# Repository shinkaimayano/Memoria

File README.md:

# Memoria

A hotswap drop-in PCB for the [V4N4G0N](https://trashman.wiki/keyboards/v4n4g0n) family of keyboards.

## Features
  
- RP2040 MCU with 16MBs (128Mbs) of flash storage.  
- Has integrated aRGB LED indicators (SK6812MINI-E), replacing the soldered single-color THT LEDs of the original.  
  - These pins are broken out if you want to add underglow as well.
- Overcurrent and ESD protection.
- Curved traces, teardrops, and a hatched copper fill for a prettier look.  

The firmware, found [here](https://github.com/shinkaimayano/Firmwares/tree/main/memoria/rev2.0), can be flashed by dragging and dropping the .uf2 file into the Mass Storage Device (MSD) that shows up on the first plug-in of the PCB. Afterwards, it is recommended to use Bootmagic (by holding down the top left key on plug-in) to put it into bootloader. You can short the two pads underneath while plugging it in as a last resort.

## Layout and Renders

This PCB supports the [Jetvan](https://trashman.wiki/pcbs/jetvan) (6.25u) and [Minisub](https://trashman.wiki/en/community/pcbs/minisub) (2.75u-2.25u-1.25u) bottom rows. The KLE can be found [here](http://www.keyboard-layout-editor.com/#/gists/7a51d1ecabd92635db48dc4a6c9a3fa1).

## Ordering

Current Status: **Working** (***Order at your own risk!***)

The following guide is for ordering these PCBs from [JLCPCB](https://jlcpcb.com/).

1. Click the "Order now" text and upload the zipped gerbers via draging-and-dropping or locating the file via your file explorer.
2. After it finishes uploading, it may or may not display a preview of what it should it look like. If it doesn't, it won't autofill in the dimensions of the PCB. Input these numbers (242.8875mm x 96.7850mm) into the dimensions box if so.
3. You can now pick out your preferred PCB color, finish, and decide if you want to remove the order number silkscreen on the PCB for a bit extra along with some other extra options you can choose.
4. Check the option for "PCB Assembly" and change the assembly side to the bottom. After that, you can select if you want to have five PCBs assembled or two of them.
   - Having five PCBs assembled compared to two is a minor price increase with the benefit of:
      - Having an easy replacement if something goes wrong.
      - Wanting to use a different case without disassembling another build.
      - Being able to give/sell to others that might want it.
5. Upload the BOM & CPL in each box respectively and select "Office Appliance and Accessories &rarr; Keyboard HS Code 847330" for the description.
6. On the next page, you can see the output of the BOM file and check if the parts are correct or if they're out of stock or not. If the hotswap sockets are out of stock, you have three options. You can either:
   - Preorder part number "C5156480" into your parts library and order the PCBs when they arrive.
   - Wait for them to restock.
   - Order without the sockets pre-assembled and solder them on yourself.
7. On the final page, you can now see a preview of where the components are going to be placed and their respective rotations based on the CPL file. Review the positions and rotations and fix them if you need to.
8. At this point, you should be now able to place your order unless you want to order other PCBs with it! Make sure to respond to any e-mails that they send.
   - I would make sure to double check the parts placement after they do their DFM analysis as they changed the rotations of the horizontal diodes even though they were correct in the order preview. (I didn't notice this beforehand and had to fix the PCBs when they arrived. This could have been remedied by selecting "Confirm Parts Placement" after checking the option for "PCB Assembly" in step 4.)

Plate files are available from [Kiser Design's](https://kiserdesigns.bigcartel.com) [Monorail](https://trashman.wiki/en/community/pcbs/monorail) repository ([here](https://github.com/KiserDesigns/monorail)). The plate layout should be either be "Jet" or "Combined" and whether to choose the compression-style plate (V4N R1/2) or the bottom/top mount plate (V3N a.k.a. Hullagon) depends on what case you are using.

- I highly recommend getting your plates cut from [P3D  Store](https://p3dstore.com/products/switch-plates) as they have several materials that are loved by the community. They currently only offer plastic plates though so:
  - If you want a metal plate, you can have them cut from either [SendCutSend](https://sendcutsend.com/) (USA) or [LaserBoost](https://www.laserboost.com/) (EU) by directly uploading the .dxf file to their website.
  - If you want a FR4 plate, you'll need to do a bit of extra work. You can watch [this tutorial](https://www.youtube.com/watch?v=VofKu8A7l3c) if don't know how to convert a .dxf file into usable gerber files. You can order these alongside the PCBs as well.
    - If you have JLCPCB fabricate them, you will most likely get slapped with a fine for needing an excess amount of time to mill out the switch cutouts, wearing out their bits in the process.

## Notes

- Debug pins (SWDIO & SWCLK) are not broken out.
  - As the bootloader is stored in the RP2040's ROM, it would be pratically impossible to brick it.
- Slightly updated the edge cuts to make it a one-to-one match to the original R3 plate file.
  - Fillets were too big and edges were off by a smidge.
- Two switches were flipped on R3 instead of putting the MCU on the bottom row for sanity reasons.
  - This shouldn't effect anything excepting needing a little more attention when installing switches.
- Changed matrix connections of two switches to prevent any chance of them shorting each other compared to previous revisions.
- Plating was added to the bottom stabilizer holes so GND can't be accidentally shorted when using screw-in stabilizers.
- The flower silkscreen was removed in favor for a user-friendly key sizing guide.
- The aRGB on the PCB are slightly off in the vertical direction compared to the plate for cleaner routing.
- The libraries used for this project are my own and [marbastlib](https://github.com/ebastler/marbastlib).
- You need at least KiCad 6 Nightly (2022-10-28 and beyond) to open the source files.

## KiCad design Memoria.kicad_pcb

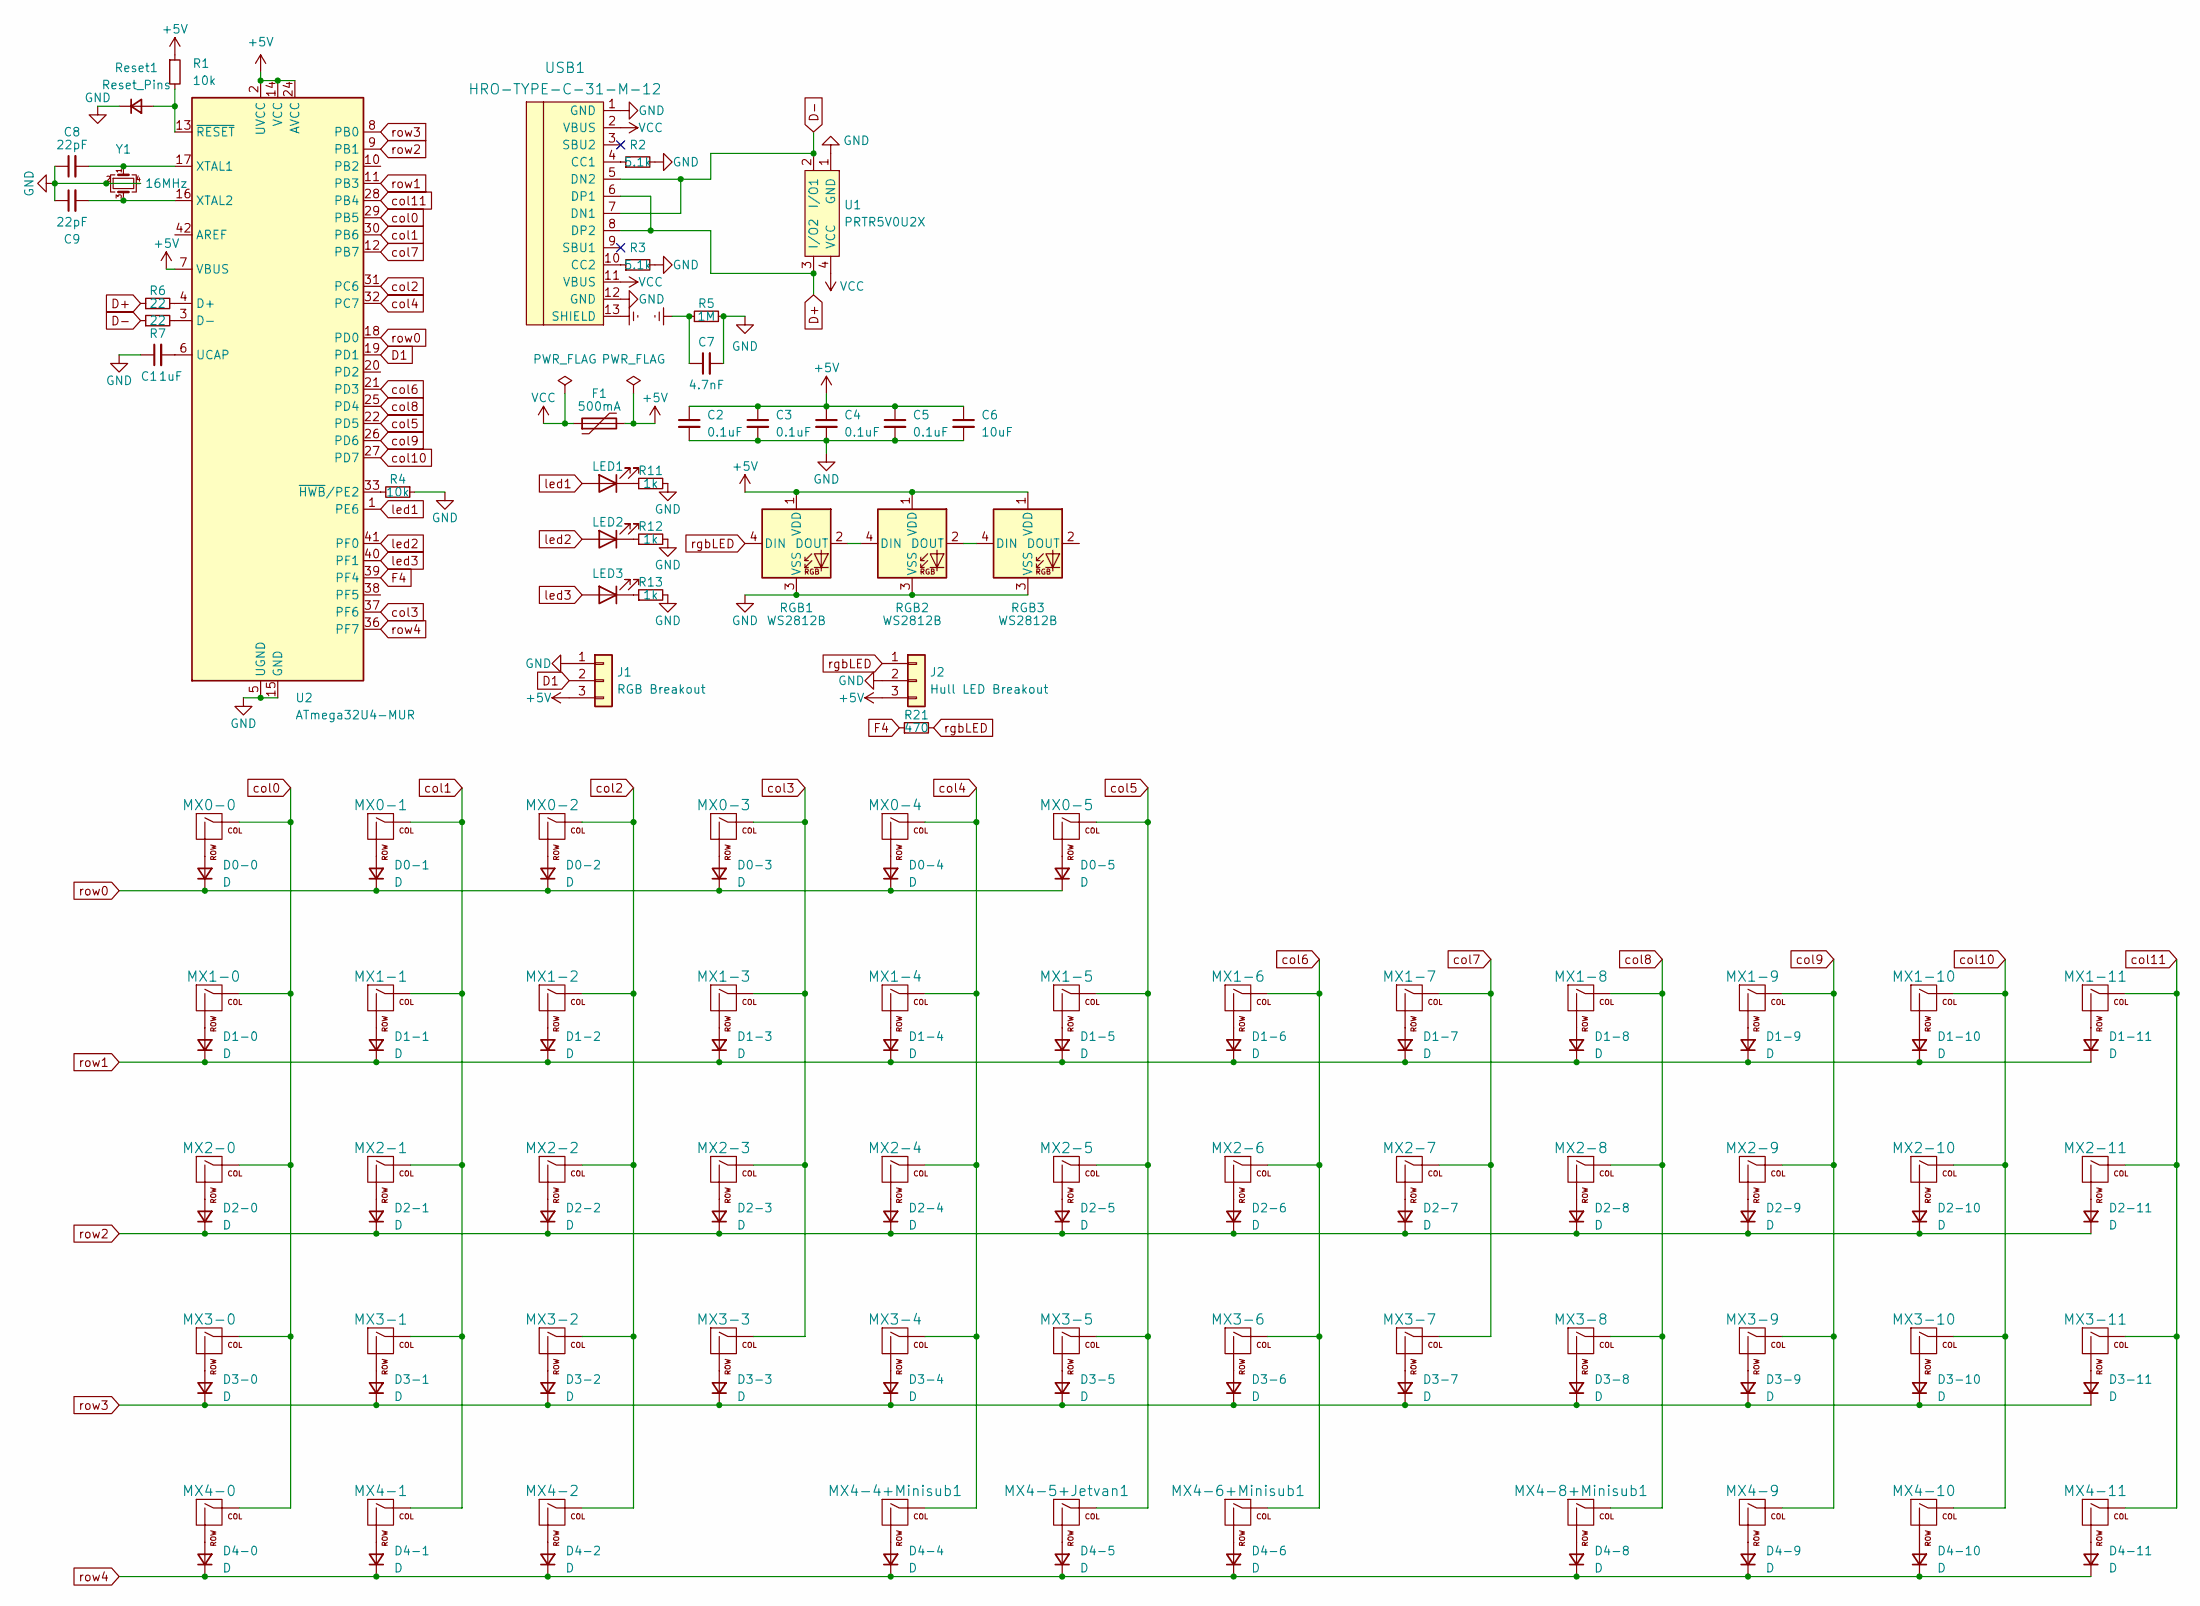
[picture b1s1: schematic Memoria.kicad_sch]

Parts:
C1: 1uF; C_0603_1608Metric
C2, C3, C4, C5: 0.1uF; C_0603_1608Metric
C6: 10uF; C_0603_1608Metric
C7: 4.7nF; C_0603_1608Metric
C8, C9: 22pF; C_0603_1608Metric
D0-0, D0-1, D0-2, D0-3, D0-4, D0-5, D1-0, D1-1, D1-2, D1-3, D1-4, D1-5, D1-6, D1-7, D1-8, D1-9, D1-10, D1-11, D2-0, D2-1, D2-2, D2-3, D2-4, D2-5, D2-6, D2-7, D2-8, D2-9, D2-10, D2-11, D3-0, D3-1, D3-2, D3-3, D3-4, D3-5, D3-6, D3-7, D3-8, D3-9, D3-10, D3-11, D4-0, D4-1, D4-2, D4-4, D4-5, D4-6, D4-8, D4-9, D4-10, D4-11: D; D_SOD-123
F1: 500mA; Fuse_1206_3216Metric
J1: RGB Breakout; PinHeader_1x03_P2.54mm_Vertical
J2: Hull LED Breakout; PinHeader_1x03_P2.54mm_Vertical
LED1, LED2, LED3: LED; LED_D3.0mm
MX0-0, MX0-1, MX0-2, MX0-3, MX0-4, MX0-5, MX1-0, MX1-1, MX1-2, MX1-3, MX1-4, MX1-5, MX1-6, MX1-7, MX1-8, MX1-9, MX1-10, MX2-1, MX2-2, MX2-3, MX2-4, MX2-5, MX2-6, MX2-7, MX2-8, MX2-9, MX2-10, MX3-1, MX3-2, MX3-3, MX3-4, MX3-5, MX3-6, MX3-7, MX3-8, MX3-9, MX3-10, MX3-11, MX4-1, MX4-9, MX4-10, MX4-11: MX-NoLED; MXOnly-1U-Hotswap
MX1-11, MX3-0: MX-NoLED; MXOnly-1.75U-Hotswap
MX2-0, MX4-0, MX4-2, MX4-8+Minisub1: MX-NoLED; MXOnly-1.25U-Hotswap
MX2-11: MX-NoLED; MXOnly-1.5U-Hotswap
MX4-4+Minisub1: MX-NoLED; MXOnly-2.75U-Hotswap-ReversedStabilizers
MX4-5+Jetvan1: MX-NoLED; MXOnly-6.25U-Hotswap-ReversedStabilizers
MX4-6+Minisub1: MX-NoLED; MXOnly-2.25U-Hotswap-ReversedStabilizers
R1, R4: 10k; R_0603_1608Metric
R2, R3: 5.1k; R_0603_1608Metric
R5: 1M; R_0603_1608Metric
R6, R7: 22; R_0805_2012Metric
R11, R12, R13: 1k; R_0805_2012Metric
R21: 470; R_0805_2012Metric
RGB1, RGB2, RGB3: WS2812B
Reset1: Reset_Pins; PinHeader_1x02_P2.54mm_Vertical
U1: PRTR5V0U2X; SOT-143B
U2: ATmega32U4-MUR; QFN-44-1EP_7x7mm_P0.5mm_EP5.2x5.2mm
USB1: HRO-TYPE-C-31-M-12; HRO-TYPE-C-31-M-12-Assembly
Y1: 16MHz; Crystal_SMD_3225-4Pin_3.2x2.5mm

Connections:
+5V: C2.1, C3.1, C4.1, C5.1, C6.1, F1.2, J1.3, J2.3, R1.1, RGB1.1 (VDD), RGB2.1 (VDD), RGB3.1 (VDD), U2.2 (UVCC), U2.7 (VBUS), U2.14 (VCC), U2.24 (AVCC), U2.34 (VCC), U2.44 (AVCC)
D1: J1.2, U2.19 (PD1)
D+: R6.1, U1.3 (I/O2), USB1.6 (DP1), USB1.8 (DP2)
D-: R7.1, U1.2 (I/O1), USB1.5 (DN2), USB1.7 (DN1)
Earth: C7.1, R5.1, USB1.13 (SHIELD)
F4: R21.1, U2.39 (PF4)
GND: C1.1, C2.2, C3.2, C4.2, C5.2, C6.2, C7.2, C8.1, C9.1, J1.1, J2.2, R2.2, R3.2, R4.1, R5.2, R11.2, R12.2, R13.2, RGB1.3 (VSS), RGB2.3 (VSS), RGB3.3 (VSS), Reset1.1 (K), U1.1 (GND), U2.5 (UGND), U2.15 (GND), U2.23 (GND), U2.35 (GND), U2.43 (GND), U2.45 (GND), USB1.1 (GND), USB1.12 (GND), Y1.2, Y1.4
unnamed: C1.2, U2.6 (UCAP)
unnamed: C8.2, U2.17 (XTAL1), Y1.1
unnamed: C9.2, U2.16 (XTAL2), Y1.3
unnamed: D0-0.2 (A), MX0-0.2 (ROW)
unnamed: D0-1.2 (A), MX0-1.2 (ROW)
unnamed: D0-2.2 (A), MX0-2.2 (ROW)
unnamed: D0-3.2 (A), MX0-3.2 (ROW)
unnamed: D0-4.2 (A), MX0-4.2 (ROW)
unnamed: D0-5.2 (A), MX0-5.2 (ROW)
unnamed: D1-0.2 (A), MX1-0.2 (ROW)
unnamed: D1-1.2 (A), MX1-1.2 (ROW)
unnamed: D1-2.2 (A), MX1-2.2 (ROW)
unnamed: D1-3.2 (A), MX1-3.2 (ROW)
unnamed: D1-4.2 (A), MX1-4.2 (ROW)
unnamed: D1-5.2 (A), MX1-5.2 (ROW)
unnamed: D1-6.2 (A), MX1-6.2 (ROW)
unnamed: D1-7.2 (A), MX1-7.2 (ROW)
unnamed: D1-8.2 (A), MX1-8.2 (ROW)
unnamed: D1-9.2 (A), MX1-9.2 (ROW)
unnamed: D1-10.2 (A), MX1-10.2 (ROW)
unnamed: D1-11.2 (A), MX1-11.2 (ROW)
unnamed: D2-0.2 (A), MX2-0.2 (ROW)
unnamed: D2-1.2 (A), MX2-1.2 (ROW)
unnamed: D2-2.2 (A), MX2-2.2 (ROW)
unnamed: D2-3.2 (A), MX2-3.2 (ROW)
unnamed: D2-4.2 (A), MX2-4.2 (ROW)
unnamed: D2-5.2 (A), MX2-5.2 (ROW)
unnamed: D2-6.2 (A), MX2-6.2 (ROW)
unnamed: D2-7.2 (A), MX2-7.2 (ROW)
unnamed: D2-8.2 (A), MX2-8.2 (ROW)
unnamed: D2-9.2 (A), MX2-9.2 (ROW)
unnamed: D2-10.2 (A), MX2-10.2 (ROW)
unnamed: D2-11.2 (A), MX2-11.2 (ROW)
unnamed: D3-0.2 (A), MX3-0.2 (ROW)
unnamed: D3-1.2 (A), MX3-1.2 (ROW)
unnamed: D3-2.2 (A), MX3-2.2 (ROW)
unnamed: D3-3.2 (A), MX3-3.2 (ROW)
unnamed: D3-4.2 (A), MX3-4.2 (ROW)
unnamed: D3-5.2 (A), MX3-5.2 (ROW)
unnamed: D3-6.2 (A), MX3-6.2 (ROW)
unnamed: D3-7.2 (A), MX3-7.2 (ROW)
unnamed: D3-8.2 (A), MX3-8.2 (ROW)
unnamed: D3-9.2 (A), MX3-9.2 (ROW)
unnamed: D3-10.2 (A), MX3-10.2 (ROW)
unnamed: D3-11.2 (A), MX3-11.2 (ROW)
unnamed: D4-0.2 (A), MX4-0.2 (ROW)
unnamed: D4-1.2 (A), MX4-1.2 (ROW)
unnamed: D4-2.2 (A), MX4-2.2 (ROW)
unnamed: D4-4.2 (A), MX4-4+Minisub1.2 (ROW)
unnamed: D4-5.2 (A), MX4-5+Jetvan1.2 (ROW)
unnamed: D4-6.2 (A), MX4-6+Minisub1.2 (ROW)
unnamed: D4-8.2 (A), MX4-8+Minisub1.2 (ROW)
unnamed: D4-9.2 (A), MX4-9.2 (ROW)
unnamed: D4-10.2 (A), MX4-10.2 (ROW)
unnamed: D4-11.2 (A), MX4-11.2 (ROW)
unnamed: LED1.1 (K), R11.1
unnamed: LED2.1 (K), R12.1
unnamed: LED3.1 (K), R13.1
unnamed: R1.2, Reset1.2 (A), U2.13 (~RESET)
unnamed: R2.1, USB1.4 (CC1)
unnamed: R3.1, USB1.10 (CC2)
unnamed: R4.2, U2.33 (~HWB/PE2)
unnamed: R6.2, U2.4 (D+)
unnamed: R7.2, U2.3 (D-)
unnamed: RGB1.2 (DOUT), RGB2.4 (DIN)
unnamed: RGB2.2 (DOUT), RGB3.4 (DIN)
VCC: F1.1, U1.4 (VCC), USB1.2 (VBUS), USB1.11 (VBUS)
col0: MX0-0.1 (COL), MX1-0.1 (COL), MX2-0.1 (COL), MX3-0.1 (COL), MX4-0.1 (COL), U2.29 (PB5)
col1: MX0-1.1 (COL), MX1-1.1 (COL), MX2-1.1 (COL), MX3-1.1 (COL), MX4-1.1 (COL), U2.30 (PB6)
col2: MX0-2.1 (COL), MX1-2.1 (COL), MX2-2.1 (COL), MX3-2.1 (COL), MX4-2.1 (COL), U2.31 (PC6)
col3: MX0-3.1 (COL), MX1-3.1 (COL), MX2-3.1 (COL), MX3-3.1 (COL), U2.37 (PF6)
col4: MX0-4.1 (COL), MX1-4.1 (COL), MX2-4.1 (COL), MX3-4.1 (COL), MX4-4+Minisub1.1 (COL), U2.32 (PC7)
col5: MX0-5.1 (COL), MX1-5.1 (COL), MX2-5.1 (COL), MX3-5.1 (COL), MX4-5+Jetvan1.1 (COL), U2.22 (PD5)
col6: MX1-6.1 (COL), MX2-6.1 (COL), MX3-6.1 (COL), MX4-6+Minisub1.1 (COL), U2.21 (PD3)
col7: MX1-7.1 (COL), MX2-7.1 (COL), MX3-7.1 (COL), U2.12 (PB7)
col8: MX1-8.1 (COL), MX2-8.1 (COL), MX3-8.1 (COL), MX4-8+Minisub1.1 (COL), U2.25 (PD4)
col9: MX1-9.1 (COL), MX2-9.1 (COL), MX3-9.1 (COL), MX4-9.1 (COL), U2.26 (PD6)
col10: MX1-10.1 (COL), MX2-10.1 (COL), MX3-10.1 (COL), MX4-10.1 (COL), U2.27 (PD7)
col11: MX1-11.1 (COL), MX2-11.1 (COL), MX3-11.1 (COL), MX4-11.1 (COL), U2.28 (PB4)
led1: LED1.2 (A), U2.1 (PE6)
led2: LED2.2 (A), U2.41 (PF0)
led3: LED3.2 (A), U2.40 (PF1)
rgbLED: J2.1, R21.2, RGB1.4 (DIN)
row0: D0-0.1 (K), D0-1.1 (K), D0-2.1 (K), D0-3.1 (K), D0-4.1 (K), D0-5.1 (K), U2.18 (PD0)
row1: D1-0.1 (K), D1-1.1 (K), D1-2.1 (K), D1-3.1 (K), D1-4.1 (K), D1-5.1 (K), D1-6.1 (K), D1-7.1 (K), D1-8.1 (K), D1-9.1 (K), D1-10.1 (K), D1-11.1 (K), U2.11 (PB3)
row2: D2-0.1 (K), D2-1.1 (K), D2-2.1 (K), D2-3.1 (K), D2-4.1 (K), D2-5.1 (K), D2-6.1 (K), D2-7.1 (K), D2-8.1 (K), D2-9.1 (K), D2-10.1 (K), D2-11.1 (K), U2.9 (PB1)
row3: D3-0.1 (K), D3-1.1 (K), D3-2.1 (K), D3-3.1 (K), D3-4.1 (K), D3-5.1 (K), D3-6.1 (K), D3-7.1 (K), D3-8.1 (K), D3-9.1 (K), D3-10.1 (K), D3-11.1 (K), U2.8 (PB0)
row4: D4-0.1 (K), D4-1.1 (K), D4-2.1 (K), D4-4.1 (K), D4-5.1 (K), D4-6.1 (K), D4-8.1 (K), D4-9.1 (K), D4-10.1 (K), D4-11.1 (K), U2.36 (PF7)

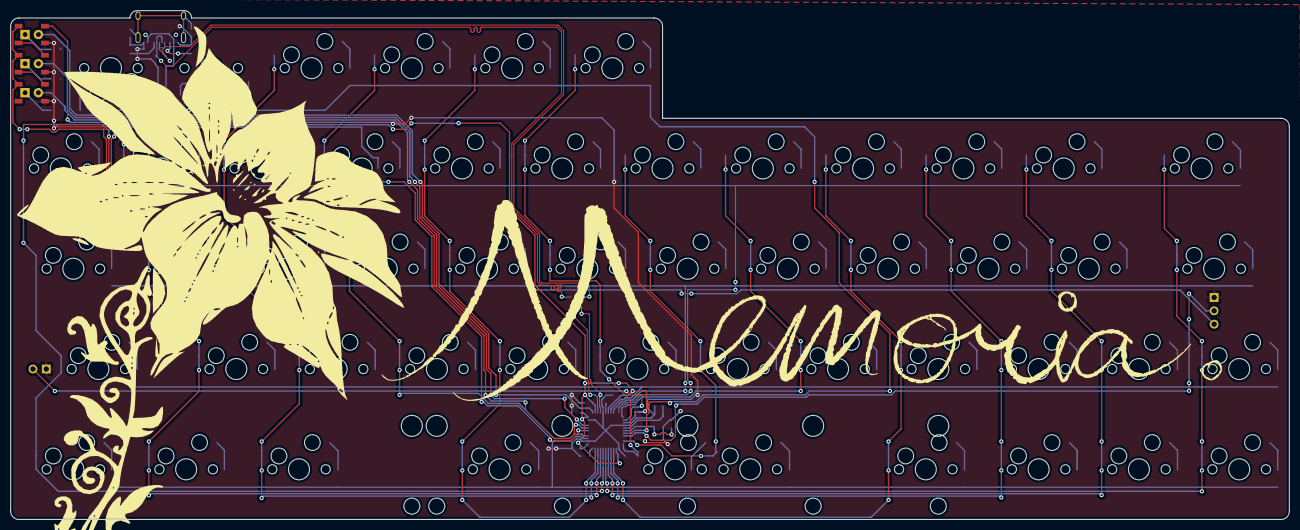
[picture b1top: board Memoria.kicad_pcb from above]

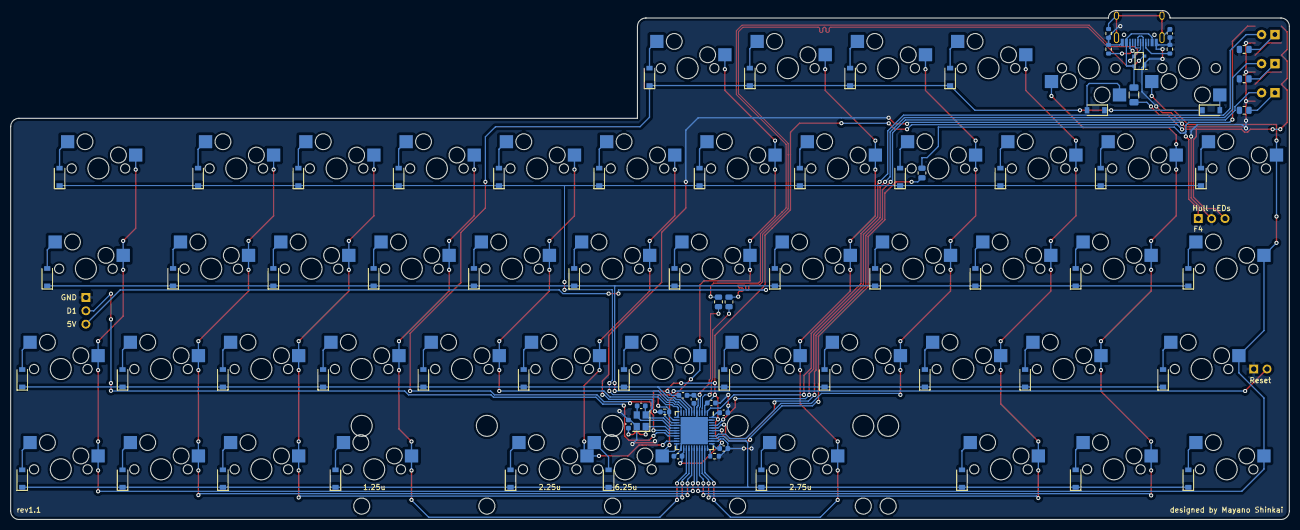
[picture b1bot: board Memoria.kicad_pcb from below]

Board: 2 copper layers, 242.9 x 96.6 mm, 138 parts (77 on the bottom side), 95 nets.

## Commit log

2022-02-03 added images.
2022-02-03 grammer
2022-02-03 clarification
2022-02-03 updated outdated silkscreen.
2022-02-04 rerouted traces near crystal
2022-02-06 final pass
2022-02-06 real final pass
2022-02-07 the final final pass
    silkscreen art, added 470 resistor, changed 1uF capacitor in BOM
2022-02-17 added termination resistors
2022-02-17 updated revision number
2022-03-10 cleanup
    moved termination resistors closer to mcu, added hotswap sockets to bom, updated readme.md
2022-03-15 skewed data line length
2022-12-28 rev 2.0 release, reorganizing of files
    this took too long aaaaaaaaa
